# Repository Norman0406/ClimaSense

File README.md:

# ClimaSense

An ESP32-based indoor environment sensor. It periodically measures temperature, humidity, CO2, VOC/NOx and air pressure and publishes the readings via MQTT. Wi-Fi is configured through a captive portal.

The picture shows the latest revision, 2.0, which is still in design. All pictures here are renders and plots of the KiCad design (`python hardware/rev-<N>/tools/gen_images.py`), not photographs.

## Revision 1.0

The first board, ordered at JLCPCB on 2026-11-20.

75 × 34 mm, two layers, powered and programmed through USB-C. It hangs on a wall with the USB cable down; the arrow on the silkscreen points up. From left to right:

- **ESP32-C6 module** with its antenna at the left edge, the status LED above it.
- **Buttons, power and USB**: BOOT and RESET, the 3.3 V converter, the USB-C socket on the bottom edge and a Qwiic connector on the top edge.
- **A milled slot**, which keeps the heat of everything on the left away from the sensors.
- **The sensors**: SCD41 (CO2) and SGP41 (VOC/NOx) at the top, because they are the two that warm up and heat rises; the SHT45 (temperature and humidity) below them at the right edge, on a tongue of its own that is cut free on three sides, with nothing underneath it; and the BMP580 (pressure) at the lower left, which gives off practically no heat.

How the board is laid out and why: [`docs/hardware/layout.md`](docs/hardware/layout.md).

## Revision 2.0 (in design)

Revision 2.0 adds a 2.13" black-and-white e-paper panel and is 103 × 34 mm. **It is still being designed and has not been built or ordered.** Its notes: [`docs/hardware/rev-2.0.md`](docs/hardware/rev-2.0.md).

The parts face the room, as on revision 1.0. The panel lies above them, on a printed frame 4.75 mm above the board that is not designed yet; its flexible tail folds back under it into a connector. The picture at the top of this page shows the panel in place; the pictures below show the board without it.

From the side, with the USB connector towards the viewer: the panel above the parts, its tail folding back under it on the right, and the SCD41, the tallest part, beside it:

The panel covers everything from the module to the display connector. The buttons and the status LED are on the top edge, and the sensors keep their arrangement behind the slot:

The back carries no parts, only the test pads:

The copper of the two layers. Most tracks run on the component side; the back is mostly ground. Both are drawn as seen from the component side, the bottom layer through the board, so the two pictures line up:

## Contents

| Folder | What |
| --- | --- |
| [`hardware/`](hardware/) | KiCad project for the PCB (designed for full fab assembly) |
| [`firmware/`](firmware/) | ESP32 firmware |
| [`docs/`](docs/) | Research and design decisions |

## Status

- **Hardware, revision 1.0:** schematic and board are finished and pass KiCad's rule checks; the order files for JLCPCB are in [`hardware/rev-1.0/fab/`](hardware/rev-1.0/fab/). Not manufactured yet, and not reviewed by a second person.
- **Hardware, revision 2.0:** in design (e-paper display above the parts, on a frame); the board routes completely and passes KiCad's rule checks, but it is not finished and not ordered.
- **Firmware:** in progress, and so far only built, not run on hardware. See [`firmware/README.md`](firmware/README.md) and [`docs/firmware/architecture.md`](docs/firmware/architecture.md).

What was decided and why: [`docs/decisions.md`](docs/decisions.md). The component research behind it: [`docs/research/hardware-options.md`](docs/research/hardware-options.md).

## Licence

MIT, for the firmware, the KiCad design and the docs: see [`LICENSE`](LICENSE). Third-party code keeps its own licence, next to it in its `vendor/` folder (so far Sensirion's Gas Index Algorithm, BSD-3-Clause).

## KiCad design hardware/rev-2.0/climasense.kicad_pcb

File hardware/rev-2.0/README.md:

# Hardware — revision 2.0 (designed, not ordered)

KiCad 10 project for ClimaSense revision 2.0: revision 1.0 plus a 2.13" e-paper display (Good Display GDEY0213B74) that lies above the components on a printed frame, its tail folded back under it into the connector J5. What the board is, its pin map, parts and open points: [`../../docs/hardware/rev-2.0.md`](../../docs/hardware/rev-2.0.md). The design review and what has been done about its findings: [`../../REVIEW.md`](../../REVIEW.md). Revision 1.0, as ordered on 2026-11-20, is in [`../rev-1.0`](../rev-1.0) and is not changed.

`climasense.kicad_sch` and `climasense.kicad_pcb` are written by `tools/gen_schematic.py` and `tools/gen_pcb.py` and have not been edited by hand in KiCad: both generators reproduce the files here. Nothing has been ordered; `fab/` is written only when the order files are needed (`tools/gen_fab.py`, steps in [`../../docs/hardware/ordering.md`](../../docs/hardware/ordering.md#revision-20)).

The files and the scripts work as in revision 1.0 (see [`../rev-1.0/README.md`](../rev-1.0/README.md)); run them from the repository root with `hardware/rev-2.0/tools/...`. Outputs go to `build/` and `fab/` in this folder; `fab/` files are named `climasense-2.0-…`, and `tools/gen_images.py` writes to `docs/images/rev-2.0/`.

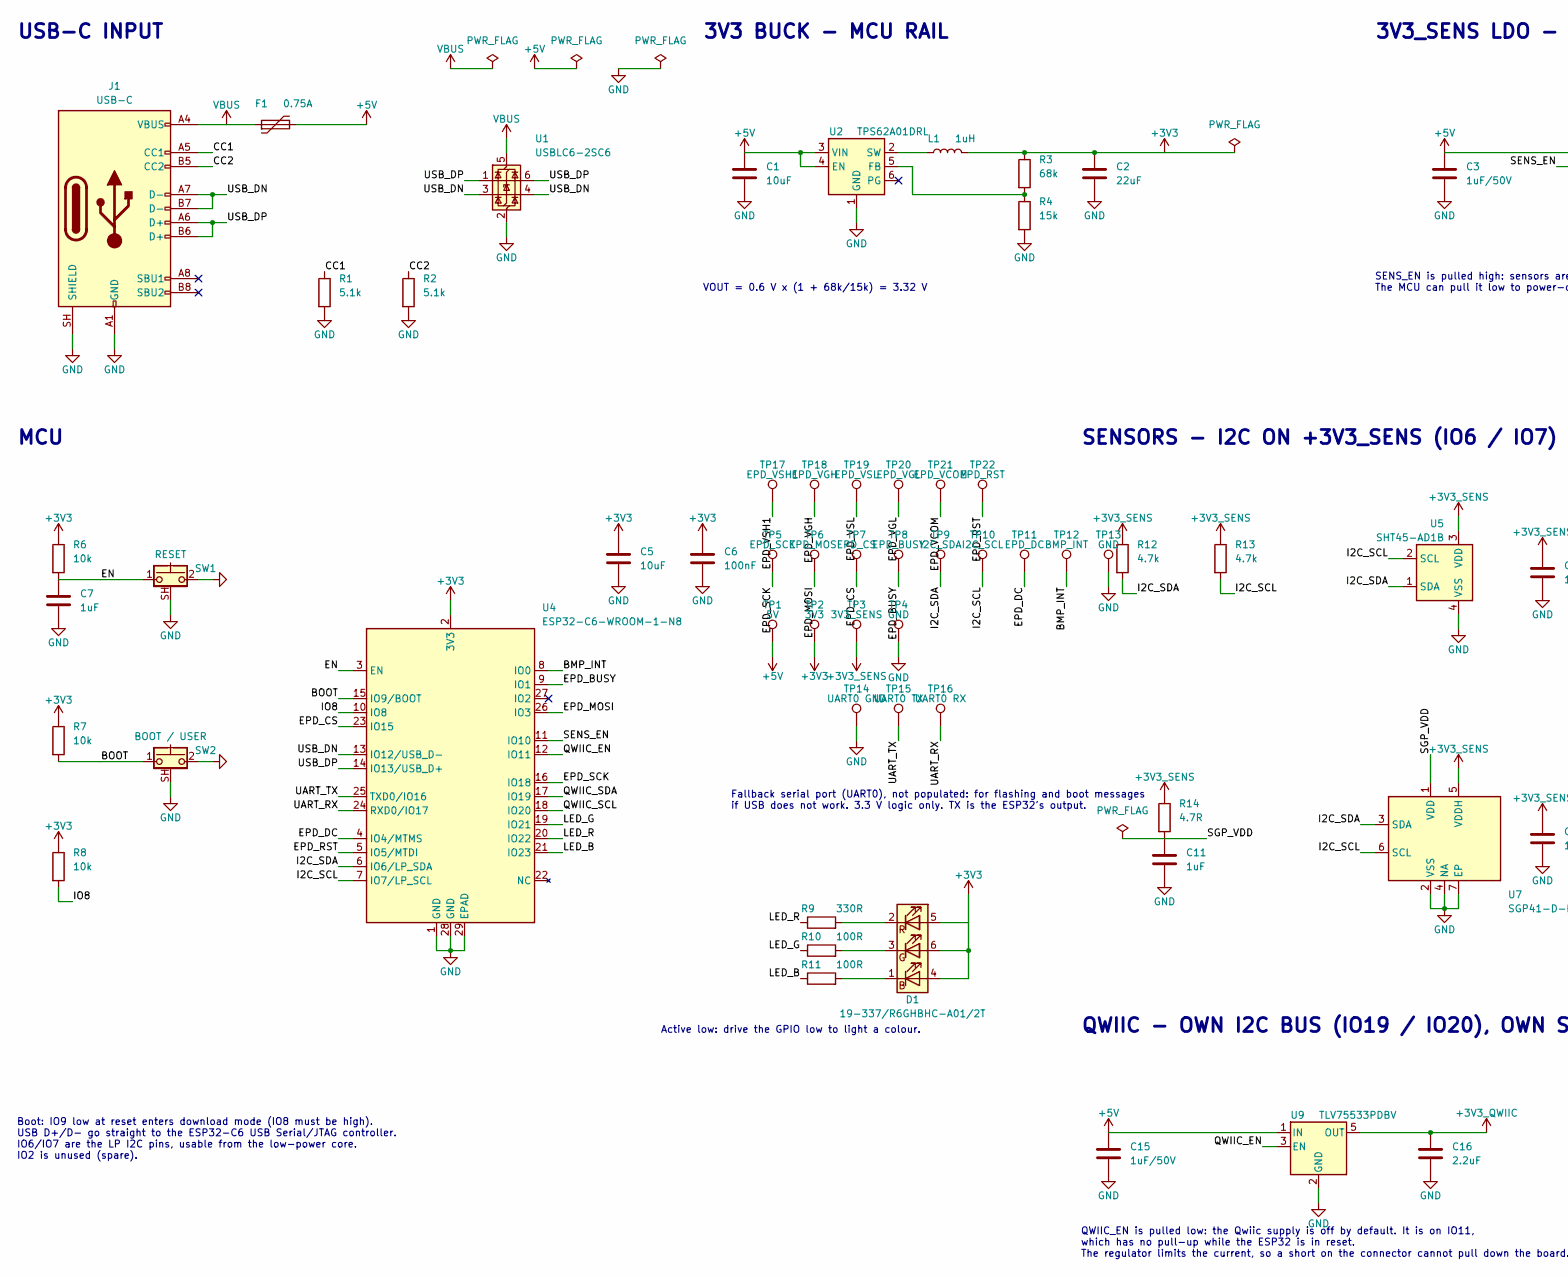
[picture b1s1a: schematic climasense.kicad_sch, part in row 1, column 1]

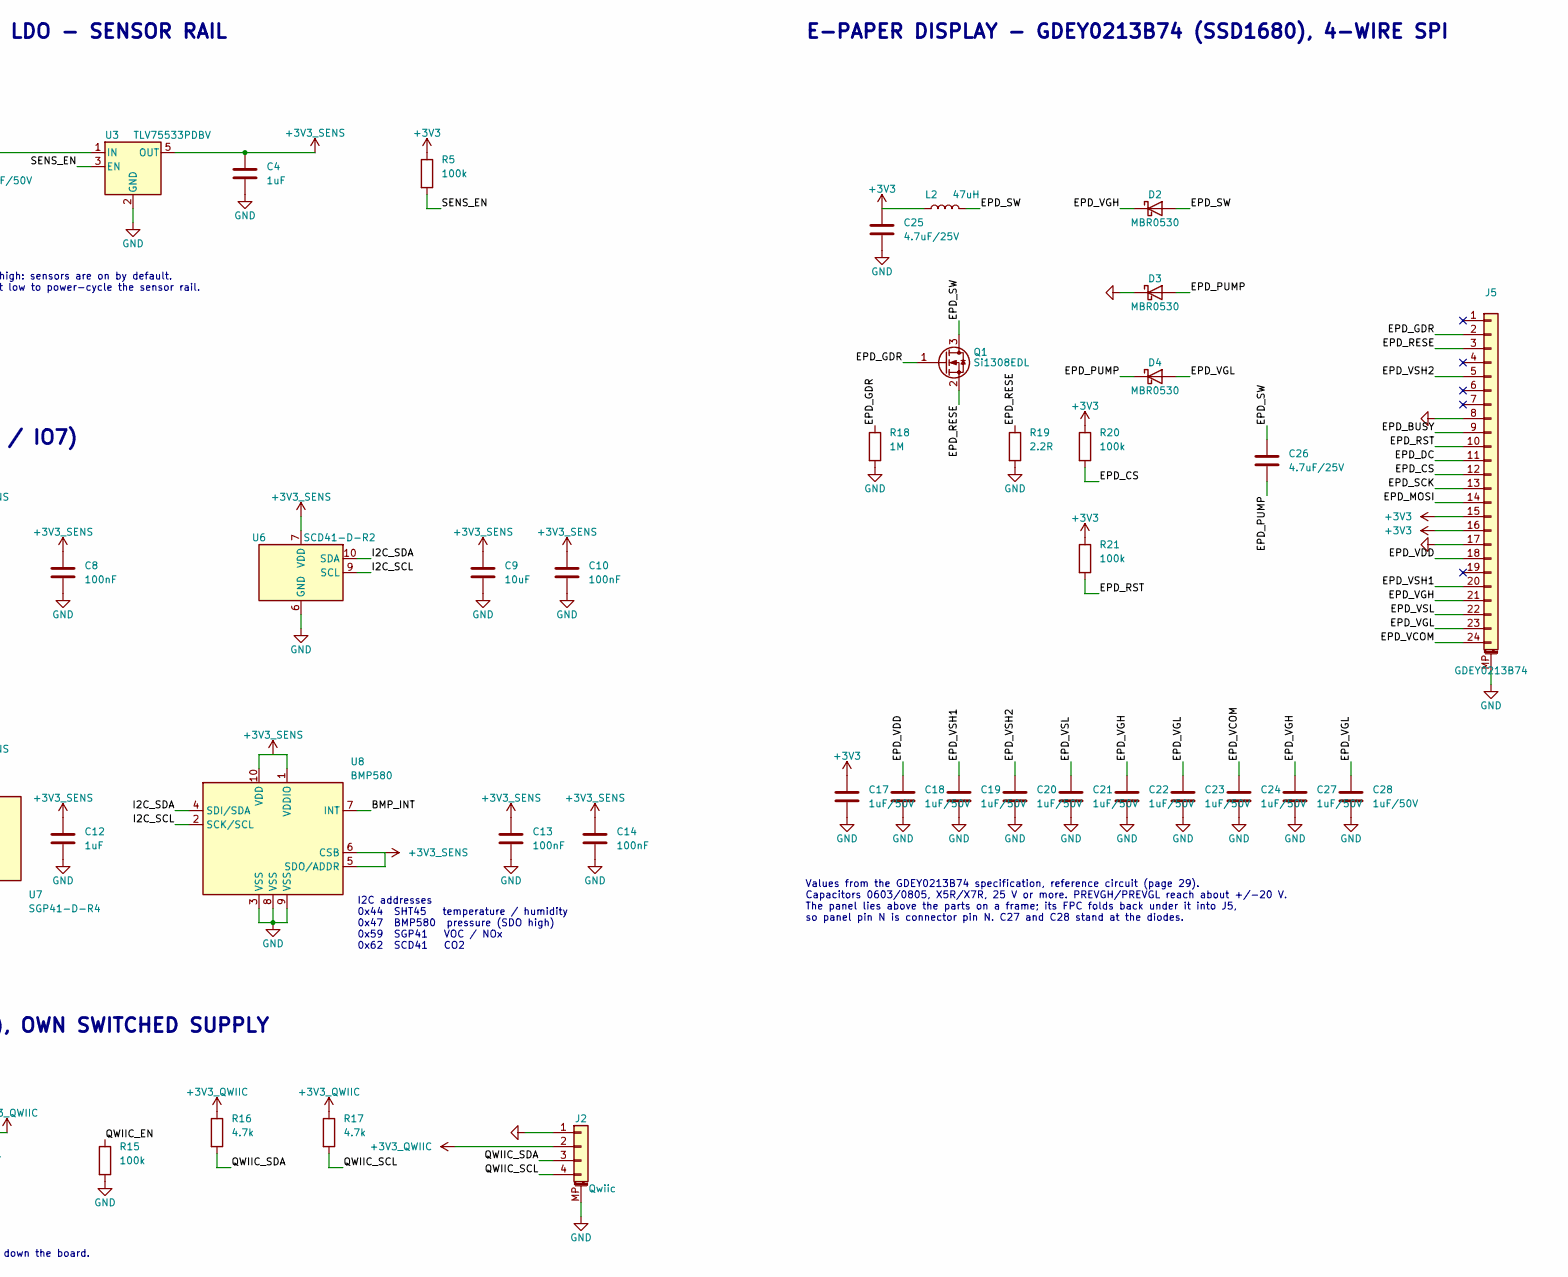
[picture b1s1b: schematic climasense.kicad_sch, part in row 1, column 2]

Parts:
C1, C5, C9: 10uF; C_0805_2012Metric; MPN CL21A106KAYNNNE; LCSC C15850
C2: 22uF; C_0805_2012Metric; MPN CL21A226MAQNNNE; LCSC C45783
C3, C15, C17, C18, C19, C20, C21, C22, C23, C24, C27, C28: 1uF/50V; C_0603_1608Metric; MPN CL10A105KB8NNNC; LCSC C15849
C4, C7, C11, C12: 1uF; C_0402_1005Metric; MPN CL05A105KA5NQNC; LCSC C52923
C6, C8, C10, C13, C14: 100nF; C_0402_1005Metric; MPN CL05B104KO5NNNC; LCSC C1525
C16: 2.2uF; C_0402_1005Metric; MPN CL05A225MQ5NSNC; LCSC C12530
C25, C26: 4.7uF/25V; C_0805_2012Metric; MPN CL21A475KAQNNNE; LCSC C1779
D1: 19-337/R6GHBHC-A01/2T; LED_RGB_Everlight_19-337_1.6x1.6mm; MPN 19-337/R6GHBHC-A01/2T; LCSC C264519
D2, D3, D4: MBR0530; D_SOD-123; MPN MBR0530T1G; LCSC C82046
F1: 0.75A; Fuse_1206_3216Metric; MPN 1206L075/16WR; LCSC C371166
J1: USB-C; USB_C_Receptacle_HRO_TYPE-C-31-M-12; MPN TYPE-C-31-M-12; LCSC C165948
J2: Qwiic; JST_SH_SM04B-SRSS-TB_1x04-1MP_P1.00mm_Horizontal; MPN SM04B-SRSS-TB(LF)(SN); LCSC C160404
J5: GDEY0213B74; Kinghelm_KH-FPC0.5-H2.0SMT-24P-QCHF_1x24-1MP_P0.50mm; MPN KH-FPC0.5-H2.0SMT-24P-QCHF; LCSC C3249999
L1: 1uH; L_1008_2520Metric; MPN DFE252012F-1R0M=P2; LCSC C435392
L2: 47uH; L_Sunlord_SWPA4030S; MPN SWPA4030S470MT; LCSC C54731
Q1: Si1308EDL; SOT-323_SC-70; MPN SI1308EDL-T1-GE3; LCSC C469327
R1, R2: 5.1k; R_0402_1005Metric; MPN 0402WGF5101TCE; LCSC C25905
R3: 68k; R_0402_1005Metric; MPN 0402WGF6802TCE; LCSC C36871
R4: 15k; R_0402_1005Metric; MPN 0402WGF1502TCE; LCSC C25756
R5, R15, R20, R21: 100k; R_0402_1005Metric; MPN 0402WGF1003TCE; LCSC C25741
R6, R7, R8: 10k; R_0402_1005Metric; MPN 0402WGF1002TCE; LCSC C25744
R9: 330R; R_0402_1005Metric; MPN 0402WGF3300TCE; LCSC C25104
R10, R11: 100R; R_0402_1005Metric; MPN 0402WGF1000TCE; LCSC C25076
R12, R13, R16, R17: 4.7k; R_0402_1005Metric; MPN 0402WGF4701TCE; LCSC C25900
R14: 4.7R; R_0402_1005Metric; MPN 0402WGF470KTCE; LCSC C25121
R18: 1M; R_0402_1005Metric; MPN 0402WGF1004TCE; LCSC C26083
R19: 2.2R; R_0402_1005Metric; MPN AC0402FR-072R2L; LCSC C226973
SW1: RESET; Alps_SKRTLAE010_SidePush; MPN SKRTLAE010; LCSC C110293
SW2: BOOT / USER; Alps_SKRTLAE010_SidePush; MPN SKRTLAE010; LCSC C110293
TP1: 5V; TestPoint_Pad_D1.0mm
TP2: 3V3; TestPoint_Pad_D1.0mm
TP3: 3V3_SENS; TestPoint_Pad_D1.0mm
TP4, TP13: GND; TestPoint_Pad_D1.0mm
TP5: EPD_SCK; TestPoint_Pad_D1.0mm
TP6: EPD_MOSI; TestPoint_Pad_D1.0mm
TP7: EPD_CS; TestPoint_Pad_D1.0mm
TP8: EPD_BUSY; TestPoint_Pad_D1.0mm
TP9: I2C_SDA; TestPoint_Pad_D1.0mm
TP10: I2C_SCL; TestPoint_Pad_D1.0mm
TP11: EPD_DC; TestPoint_Pad_D1.0mm
TP12: BMP_INT; TestPoint_Pad_D1.0mm
TP14: UART0 GND; TestPoint_Pad_D1.0mm
TP15: UART0 TX; TestPoint_Pad_D1.0mm
TP16: UART0 RX; TestPoint_Pad_D1.0mm
TP17: EPD_VSH1; TestPoint_Pad_D1.0mm
TP18: EPD_VGH; TestPoint_Pad_D1.0mm
TP19: EPD_VSL; TestPoint_Pad_D1.0mm
TP20: EPD_VGL; TestPoint_Pad_D1.0mm
TP21: EPD_VCOM; TestPoint_Pad_D1.0mm
TP22: EPD_RST; TestPoint_Pad_D1.0mm
U1: USBLC6-2SC6; SOT-23-6; MPN USBLC6-2SC6; LCSC C7519
U2: TPS62A01DRL; SOT-563; MPN TPS62A01DRLR; LCSC C5157937
U3, U9: TLV75533PDBV; SOT-23-5; MPN TLV75533PDBVR; LCSC C404027
U4: ESP32-C6-WROOM-1-N8; ESP32-C6-WROOM-1; MPN ESP32-C6-WROOM-1-N8; LCSC C5366877
U5: SHT45-AD1B; Sensirion_DFN-4_1.5x1.5mm_P0.8mm_SHT4x_NoCentralPad; MPN SHT45-AD1B-R2; LCSC C5221601
U6: SCD41-D-R2; Sensirion_SCD4x-1EP_10.1x10.1mm_P1.25mm_EP4.8x4.8mm; MPN SCD41-D-R2; LCSC C3659294
U7: SGP41-D-R4; Sensirion_DFN-6-1EP_2.44x2.44mm_P0.8mm_EP1.25x1.7mm; MPN SGP41-D-R4; LCSC C3659325
U8: BMP580; Bosch_LGA-10_2x2mm_P0.5mm_BMP580; MPN BMP580; LCSC C22391138

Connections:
+3V3: C2.1, C5.1, C6.1, C17.1, C25.1, D1.4 (BA), D1.5 (RA), D1.6 (GA), J5.15, J5.16, L1.2, L2.1, R3.1, R5.1, R6.1, R7.1, R8.1, R20.1, R21.1, TP2.1, U4.2 (3V3)
+3V3_QWIIC: C16.1, J2.2, R16.1, R17.1, U9.5 (OUT)
+3V3_SENS: C4.1, C8.1, C9.1, C10.1, C12.1, C13.1, C14.1, R12.1, R13.1, R14.1, TP3.1, U3.5 (OUT), U5.3 (VDD), U6.7 (VDD), U6.19 (VDD), U7.5 (VDDH), U8.1 (VDDIO), U8.5 (SDO/ADDR), U8.6 (CSB), U8.10 (VDD)
+5V: C1.1, C3.1, C15.1, F1.2, TP1.1, U2.3 (VIN), U2.4 (EN), U3.1 (IN), U9.1 (IN)
/BMP_INT: TP12.1, U4.8 (IO0), U8.7 (INT)
/BOOT: R7.2, SW2.1, U4.15 (IO9/BOOT)
/CC1: J1.A5 (CC1), R1.1
/CC2: J1.B5 (CC2), R2.1
/EN: C7.1, R6.2, SW1.1, U4.3 (EN)
/EPD_BUSY: J5.9, TP8.1, U4.9 (IO1)
/EPD_CS: J5.12, R20.2, TP7.1, U4.23 (IO15)
/EPD_DC: J5.11, TP11.1, U4.4 (IO4/MTMS)
/EPD_GDR: J5.2, Q1.1 (G), R18.1
/EPD_MOSI: J5.14, TP6.1, U4.26 (IO3)
/EPD_PUMP: C26.2, D3.2 (A), D4.1 (K)
/EPD_RESE: J5.3, Q1.2 (S), R19.1
/EPD_RST: J5.10, R21.2, TP22.1, U4.5 (IO5/MTDI)
/EPD_SCK: J5.13, TP5.1, U4.16 (IO18)
/EPD_SW: C26.1, D2.2 (A), L2.2, Q1.3 (D)
/EPD_VCOM: C24.1, J5.24, TP21.1
/EPD_VDD: C18.1, J5.18
/EPD_VGH: C22.1, C27.1, D2.1 (K), J5.21, TP18.1
/EPD_VGL: C23.1, C28.1, D4.2 (A), J5.23, TP20.1
/EPD_VSH1: C19.1, J5.20, TP17.1
/EPD_VSH2: C20.1, J5.5
/EPD_VSL: C21.1, J5.22, TP19.1
/I2C_SCL: R13.2, TP10.1, U4.7 (IO7/LP_SCL), U5.2 (SCL), U6.9 (SCL), U7.6 (SCL), U8.2 (SCK/SCL)
/I2C_SDA: R12.2, TP9.1, U4.6 (IO6/LP_SDA), U5.1 (SDA), U6.10 (SDA), U7.3 (SDA), U8.4 (SDI/SDA)
/IO8: R8.2, U4.10 (IO8)
/LED_B: R11.1, U4.21 (IO23)
/LED_G: R10.1, U4.19 (IO21)
/LED_R: R9.1, U4.20 (IO22)
/QWIIC_EN: R15.1, U4.12 (IO11), U9.3 (EN)
/QWIIC_SCL: J2.4, R17.2, U4.18 (IO20)
/QWIIC_SDA: J2.3, R16.2, U4.17 (IO19)
/SENS_EN: R5.2, U3.3 (EN), U4.11 (IO10)
/SGP_VDD: C11.1, R14.2, U7.1 (VDD)
/UART_RX: TP16.1, U4.24 (RXD0/IO17)
/UART_TX: TP15.1, U4.25 (TXD0/IO16)
/USB_DN: J1.A7 (D-), J1.B7 (D-), U1.3 (I/O2), U1.4 (I/O2), U4.13 (IO12/USB_D-)
/USB_DP: J1.A6 (D+), J1.B6 (D+), U1.1 (I/O1), U1.6 (I/O1), U4.14 (IO13/USB_D+)
GND: C1.2, C2.2, C3.2, C4.2, C5.2, C6.2, C7.2, C8.2, C9.2, C10.2, C11.2, C12.2, C13.2, C14.2, C15.2, C16.2, C17.2, C18.2, C19.2, C20.2, C21.2, C22.2, C23.2, C24.2, C25.2, C27.2, C28.2, D3.1 (K), J1.A1 (GND), J1.A12 (GND), J1.B1 (GND), J1.B12 (GND), J1.SH (SHIELD), J2.1, J2.MP (MountPin), J5.8, J5.17, J5.MP (MountPin), R1.2, R2.2, R4.2, R15.2, R18.2, R19.2, SW1.2, SW1.SH (B), SW2.2, SW2.SH (B), TP4.1, TP13.1, TP14.1, U1.2 (GND), U2.1 (GND), U3.2 (GND), U4.1 (GND), U4.28 (GND), U4.29 (EPAD), U5.4 (VSS), U6.6 (GND), U6.20 (GND), U6.21 (GND), U7.2 (VSS), U7.4 (NA), U7.7 (EP), U8.3 (VSS), U8.8 (VSS), U8.9 (VSS), U9.2 (GND)
unnamed: D1.1 (BK), R11.2
unnamed: D1.3 (GK), R10.2
unnamed: D1.2 (RK), R9.2
unnamed: R3.2, R4.1, U2.5 (FB)
unnamed: L1.1, U2.2 (SW)
VBUS: F1.1, J1.A4 (VBUS), J1.A9 (VBUS), J1.B4 (VBUS), J1.B9 (VBUS), U1.5 (VBUS)

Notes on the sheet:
Values from the GDEY0213B74 specification, reference circuit (page 29). Capacitors 0603/0805, X5R/X7R, 25 V or more. PREVGH/PREVGL reach about +/-20 V. The panel lies above the parts on a frame; its FPC folds back under it into J5, so panel pin N is connector pin N. C27 and C28 stand at the diodes.
3V3 BUCK - MCU RAIL
3V3_SENS LDO - SENSOR RAIL
I2C addresses 0x44 SHT45 temperature / humidity 0x47 BMP580 pressure (SDO high) 0x59 SGP41 VOC / NOx 0x62 SCD41 CO2
Boot: IO9 low at reset enters download mode (IO8 must be high). USB D+/D- go straight to the ESP32-C6 USB Serial/JTAG controller. IO6/IO7 are the LP I2C pins, usable from the low-power core. IO2 is unused (spare).
E-PAPER DISPLAY - GDEY0213B74 (SSD1680), 4-WIRE SPI
USB-C INPUT
SENS_EN is pulled high: sensors are on by default. The MCU can pull it low to power-cycle the sensor rail.
VOUT = 0.6 V x (1 + 68k/15k) = 3.32 V
Active low: drive the GPIO low to light a colour.
MCU
SENSORS - I2C ON +3V3_SENS (IO6 / IO7)
QWIIC - OWN I2C BUS (IO19 / IO20), OWN SWITCHED SUPPLY
QWIIC_EN is pulled low: the Qwiic supply is off by default. It is on IO11, which has no pull-up while the ESP32 is in reset. The regulator limits the current, so a short on the connector cannot pull down the board.
Fallback serial port (UART0), not populated: for flashing and boot messages if USB does not work. 3.3 V logic only. TX is the ESP32's output.

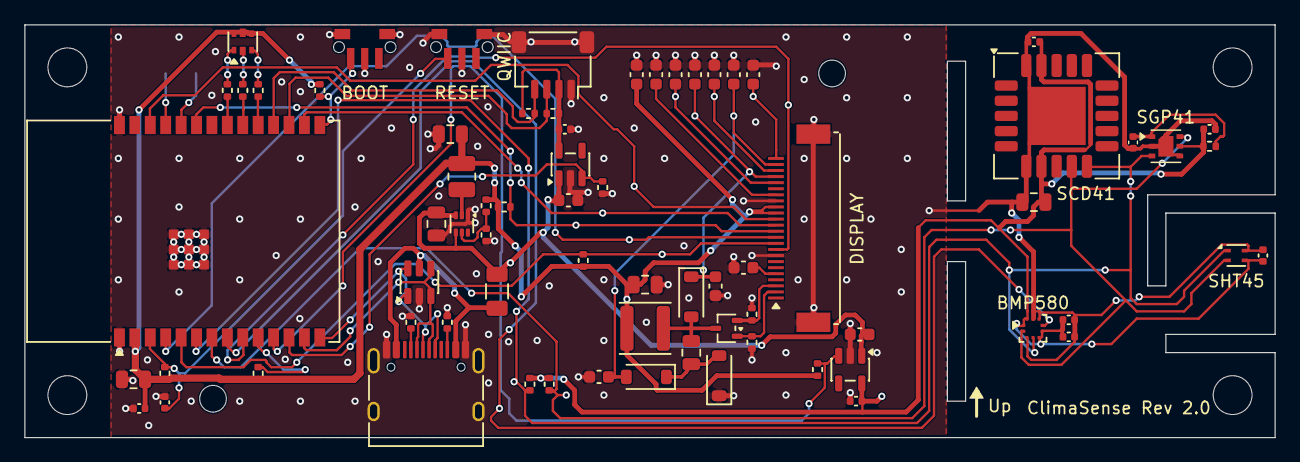
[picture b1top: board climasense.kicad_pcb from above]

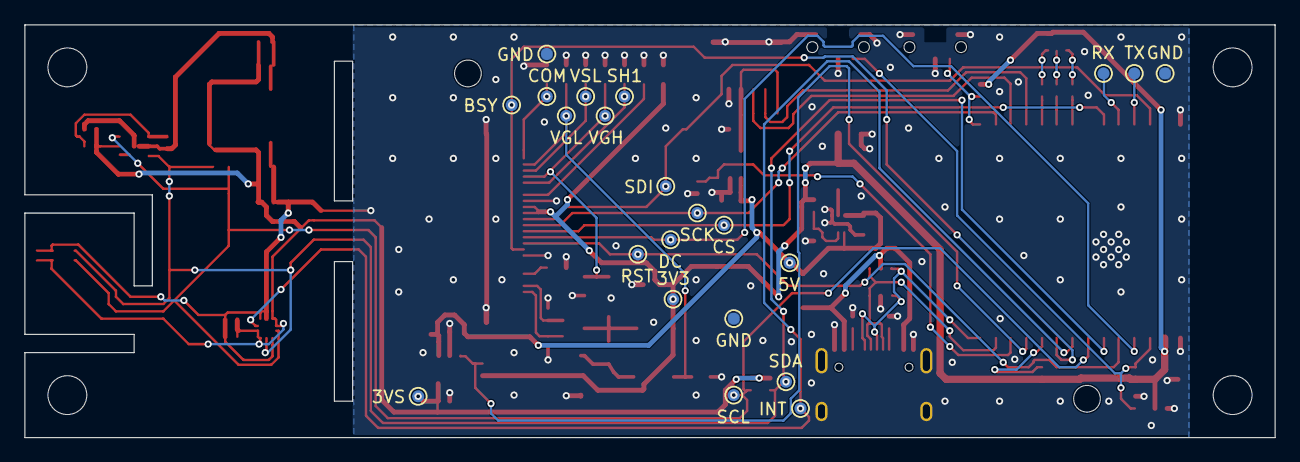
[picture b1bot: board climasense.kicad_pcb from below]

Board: 2 copper layers, 103.0 x 34.0 mm, 101 parts (22 on the bottom side), 48 nets.

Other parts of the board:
FH1, FH2: frame; MountingHole_2.2mm_M2
H1, H2, H3, H4: M3; MountingHole_3.2mm_M3
PNL1: GDEY0213B74
PNL2: FPC tail

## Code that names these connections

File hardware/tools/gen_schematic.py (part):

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    u_esd = sch.add("Power_Protection:USBLC6-2SC6", "U1", "USBLC6-2SC6", 109.22, 48.26,
                    fields={"LCSC": "C7519", "MPN": "USBLC6-2SC6"},
                    ref_at=(5.08, -7.62, "left"), value_at=(5.08, -5.08, "left"))
    sch.label(u_esd, "1", "USB_DP")
    sch.label(u_esd, "6", "USB_DP")
    sch.label(u_esd, "3", "USB_DN")
    sch.label(u_esd, "4", "USB_DN")
    sch.power(u_esd, "5", "VBUS")
    sch.power(u_esd, "2", "GND")

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    sch.power_at(279.4, lin[1], "+5V", (0, -1))
    c_lin = cap("1uF", 279.4, lin[1] + 3.81)
    sch.power_at(*c_lin.pos(2), "GND", (0, 1))
    sch.label(u_ldo, "3", "SENS_EN")
    sch.power(u_ldo, "2", "GND")
    lout = u_ldo.pos(5)
    sch.wire(lout, (330.2, lout[1]))
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    j3 = sch.add("Connector_Generic:Conn_01x03", "J3", "UART0", 172.72, 147.32,
                 footprint="climasense:PinHeader_1x03_P2.54mm_NotFitted", in_bom=False, dnp=True)
    sch.power(j3, "1", "GND", 17.78)
    sch.label(j3, "2", "UART_TX")
    sch.label(j3, "3", "UART_RX")
    sch.text(149.86, 162.56,
             "Fallback serial port (UART0), not populated: for flashing and boot messages\\n"
             "if USB does not work. 3.3 V logic only. TX is the ESP32's output.", size=1.27)
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    sch.junction(xa, ya[1])
    sch.wire((xa, ya[0]), (xa, ya[0] - 5.08))
    sch.power_at(xa, ya[0] - 5.08, "+3V3", (0, -1))
    for pin, value, net in (("2", "330R", "LED_R"), ("3", "100R", "LED_G"), ("1", "100R", "LED_B")):
        k = led.pos(pin)
        r = res(value, k[0] - 11.43, k[1], horizontal=True)
        sch.wire(r.pos(2), k)
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
    u_sht = sch.add("Sensor_Humidity:SHT4x", "U5", "SHT45-AD1B", 279.4, 119.38,
                    fields={"LCSC": "C5221601", "MPN": "SHT45-AD1B-R2"})
    sch.label(u_sht, "1", "I2C_SDA")
    sch.label(u_sht, "2", "I2C_SCL")
    sch.power(u_sht, "3", "+3V3_SENS")
    sch.power(u_sht, "4", "GND")
    cap_between("100nF", 297.18, 119.38, "+3V3_SENS")

    u_scd = sch.add("Sensor_Gas:SCD41-D-R2", "U6", "SCD41-D-R2", 340.36, 119.38,
                    fields={"LCSC": "C3659294", "MPN": "SCD41-D-R2"})
    sch.label(u_scd, "10", "I2C_SDA")
    sch.label(u_scd, "9", "I2C_SCL")
    sch.power(u_scd, "7", "+3V3_SENS")
    sch.power(u_scd, "6", "GND")
    cap_between("10uF", 373.38, 119.38, "+3V3_SENS")
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    u_sgp = sch.add("climasense:SGP41", "U7", "SGP41-D-R4", 279.4, 167.64,
                    fields={"LCSC": "C3659325", "MPN": "SGP41-D-R4"},
                    ref_at=(11.43, 10.16, "left"), value_at=(11.43, 12.7, "left"))
    sch.label(u_sgp, "3", "I2C_SDA")
    sch.label(u_sgp, "6", "I2C_SCL")
    sch.label(u_sgp, "1", "SGP_VDD", 5.08)
    sch.power(u_sgp, "5", "+3V3_SENS")
    g = [sch.stub(u_sgp, p)[0] for p in ("2", "4", "7")]
    sch.wire(g[0], g[1])
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    sch.wire(n_sgp, (n_sgp[0] - 7.62, n_sgp[1]))
    sch.flag_at(n_sgp[0] - 7.62, n_sgp[1])
    sch.wire(n_sgp, (n_sgp[0] + 7.62, n_sgp[1]))
    sch.label_at(n_sgp[0] + 7.62, n_sgp[1], "SGP_VDD", 0)
    cap_between("1uF", 297.18, 167.64, "+3V3_SENS")

    u_bmp = sch.add("climasense:BMP580", "U8", "BMP580", 335.28, 167.64,
                    fields={"LCSC": "C22391138", "MPN": "BMP580"})
    sch.label(u_bmp, "4", "I2C_SDA")
    sch.label(u_bmp, "2", "I2C_SCL")
    sch.label(u_bmp, "7", "BMP_INT")
    v = [sch.stub(u_bmp, p)[0] for p in ("10", "1")]
    mid = ((v[0][0] + v[1][0]) / 2, v[0][1])
    sch.wire(v[0], mid)
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                 footprint="climasense:PinHeader_1x05_P2.54mm_NotFitted", in_bom=False, dnp=True)
    sch.power(j4, "1", "GND", 17.78)
    sch.power(j4, "2", "+3V3_SENS", 22.86)
    sch.label(j4, "3", "I2C_SDA")
    sch.label(j4, "4", "I2C_SCL")
    sch.label(j4, "5", "BMP_INT")

    sch.text(350.52, 187.96,
             "I2C addresses\\n"
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    sch.power_at(218.44, qin[1], "+5V", (0, -1))
    c_qin = cap("1uF", 218.44, qin[1] + 3.81)
    sch.power_at(*c_qin.pos(2), "GND", (0, 1))
    sch.label(u_q, "3", "QWIIC_EN")
    sch.power(u_q, "2", "GND")
    qout = u_q.pos(5)
    sch.wire(qout, (276.86, qout[1]))
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    sch.power_at(*c_qout.pos(2), "GND", (0, 1))
    # pulled low: the Qwiic supply is off until the firmware turns it on
    r_qen = res("100k", 304.8, 226.06)
    sch.label_at(*r_qen.pos(1), "QWIIC_EN", 0)
    sch.power_at(*r_qen.pos(2), "GND", (0, 1))
    pullup("4.7k", 325.12, 220.98, "+3V3_QWIIC", "QWIIC_SDA")
    pullup("4.7k", 345.44, 220.98, "+3V3_QWIIC", "QWIIC_SCL")
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                 fields={"LCSC": "C160404", "MPN": "SM04B-SRSS-TB(LF)(SN)"})
    sch.power(j2, "1", "GND", 5.08)
    sch.power(j2, "2", "+3V3_QWIIC", 17.78)
    sch.label(j2, "3", "QWIIC_SDA")
    sch.label(j2, "4", "QWIIC_SCL")
    sch.power(j2, "MP", "GND")
    sch.text(213.36, 243.84,
             "QWIIC_EN is pulled low: the Qwiic supply is off by default. It is on IO11,\\n"
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    sch.power_at(*c_bin.pos(2), "GND", (0, 1))
    lsw = l2.pos(2)
    sch.wire(lsw, (lsw[0] + 2.54, lsw[1]))
    sch.label_at(lsw[0] + 2.54, lsw[1], "EPD_SW", 0)

    q1 = sch.add("Transistor_FET:Si1308EDL", "Q1", "Si1308EDL", 457.2, 81.28,
                 fields={"LCSC": "C469327", "MPN": "SI1308EDL-T1-GE3"})
    sch.label(q1, "3", "EPD_SW")
    sch.label(q1, "1", "EPD_GDR")
    sch.label(q1, "2", "EPD_RESE")
    r_gate = res("1M", 444.5, 96.52)
    sch.label_at(*r_gate.pos(1), "EPD_GDR", 90)
    sch.power_at(*r_gate.pos(2), "GND", (0, 1))
    r_sense = res("2.2R", 469.9, 96.52)
    sch.label_at(*r_sense.pos(1), "EPD_RESE", 90)
    sch.power_at(*r_sense.pos(2), "GND", (0, 1))

    diodes = []
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    c_pump = cap("4.7uF/25V", 515.62, 99.06)
    top = c_pump.pos(1)
    sch.wire(top, (top[0], top[1] - 2.54))
    sch.label_at(top[0], top[1] - 2.54, "EPD_SW", 90)
    bot = c_pump.pos(2)
    sch.wire(bot, (bot[0], bot[1] + 2.54))
    sch.label_at(bot[0], bot[1] + 2.54, "EPD_PUMP", 270)

    sch.text(431.8, 182.88,
             "Values from the GDEY0213B74 specification, reference circuit (page 29).\\n"
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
